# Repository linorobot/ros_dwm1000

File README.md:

first of all this is an awesome project guys you can edit it and make it more better.
this is a positioning system which will work indoor and outdoor both.
hope u all like it:)

# ros_dwm1000

ROS Indoor/Outdoor Positioning System based on Decawave's DWM1000 Ultra Wide Band transceivers.
The whole system was tested indoors with 3 anchors and 1 tag. Technically this should work outdoors as well.

### Hardware
Both anchors and tags use the same circuit board. The board houses the UWB transceiver, an Arduino Pro Mini 3.3V and a built-in USB
Male so you can plug it straight to a power bank and deploy the anchors remotely.

1. If you wish to fabricate the PCB, the Gerber files are included /hardware/pcb/fabricate.
Seeedstudio's DRU for 2-layer board was used to verify the design.

2. The DWM1000 Arduino library  uses random address for the anchors and doesn't support arbitrary addresses.
You need to edit https://github.com/grassjelly/ros_dwm1000/blob/master/hardware/firmware/anchor/lib/DW1000/DW1000Ranging.cpp#L166-L167 every time you upload the
anchor codes to have unique address per anchor from:

    ```c++
    _currentShortAddress[0] = random(0, 256);
    _currentShortAddress[1] = random(0, 256);
    ```
    to the address you want (ie. address: '01'):

    ```c++
    _currentShortAddress[0] = 1;
    _currentShortAddress[1] = 0;
    ```

### Installation
1. Install dependencies

    ```sh
    $ pip install localization
    $ pip install scipy
    $ pip install shapely
    ```

2. Install map_server

    ```sh
    $ sudo apt-get install ros-indigo-map-server
    ```

3. Build the package

    ```sh
    $ cd ~/catkin_ws
    $ catkin_make
    ```

### Defining TF
1. You need to define the transforms from map to each anchor's frame. You can run map_server and load your map to identify
the exact points you want your anchors placed. Open RVIZ and click on the location of each anchor by using "Publish Points".

2. Once you get the exact location of each anchor, add the transforms in /launch/tf.launch file. Take note that the frame_id of
each anchor must be the same as the address defined in Arduino (_currentShortAddress[]).

### Usage
1. Run localize.launch:			

    ```sh
    $ roslaunch ros_dwm1000 localize.launch
    ```

### Parameters
##### serial_port(default: '/dev/ttyUSB0')
Tag's serial port.

##### frame_id(default: 'uwb_tag')
Tag's frame_id when transform's published from map to tag.

##### req_anchor(default: 3)
The mininum number of anchors the system must find before performing trilateration between anchors. Increase this if you want to improve the accuracy. This can be tweaked down to a minimum of 2 anchors. Each tag can only support up to 4 anchors now.

##### min_range(default: 0.5)
The minimum probable distance from an anchor to a tag to prevent false reading. For example, if your anchor is hanging 1 m away from
the floor, it makes sense to put 1 meter as minimum range since there's no way it will range less than 1 meter.

##### max_range(default: 10.0)
The maximum probable distance from an anchor to a tag to prevent false reading. For example, if your anchors are placed in 8 meter x 8 meter room,
you can set the max_range less than or equal the hypotenuse of the room since ranges won't get any longer than that.

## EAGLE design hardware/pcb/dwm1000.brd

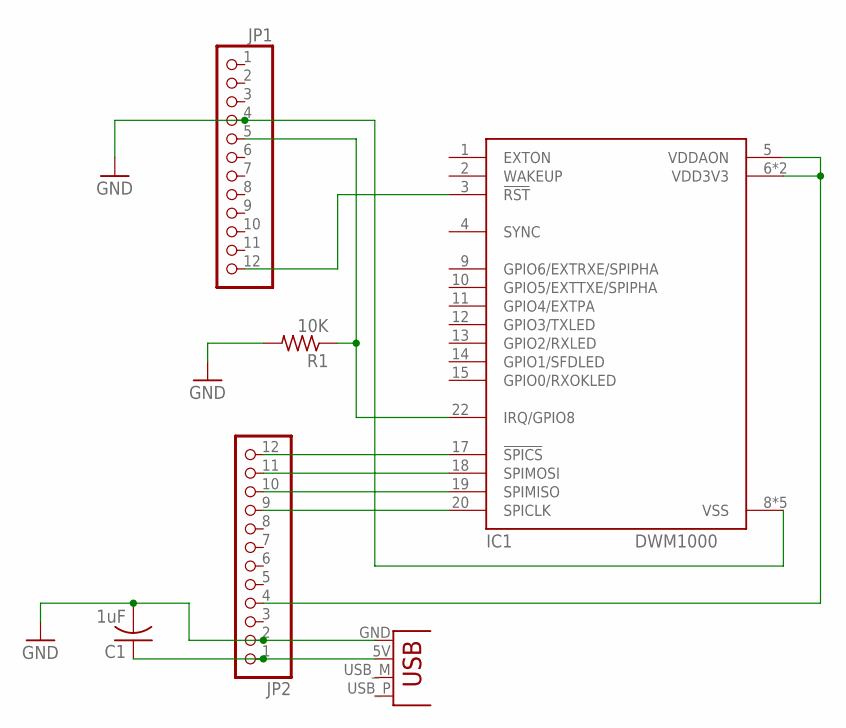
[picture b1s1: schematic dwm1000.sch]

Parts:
C1: 1uF; C025-024X044
IC1: DWM1000
JP1, JP2: PINHD-1X12; 1X12
JP3: USBPCB; USB-A-PCB
R1: 10K; 0207/7

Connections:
GND: C1.2, IC1.8 (VSS), IC1.16 (VSS), IC1.21 (VSS), IC1.23 (VSS), IC1.24 (VSS), JP1.4, JP2.2, JP3.GND, R1.2
unnamed: IC1.3 (!RST), JP1.12
unnamed: IC1.17 (!SPICS), JP2.12
unnamed: IC1.18 (SPIMOSI), JP2.11
unnamed: IC1.20 (SPICLK), JP2.9
unnamed: IC1.19 (SPIMISO), JP2.10
unnamed: IC1.22 (IRQ/GPIO8), JP1.5, R1.1
unnamed: C1.1, JP2.1, JP3.5V (VBUS)
unnamed: IC1.5 (VDDAON), IC1.6 (VDD3V3), IC1.7 (VDD3V3), JP2.4

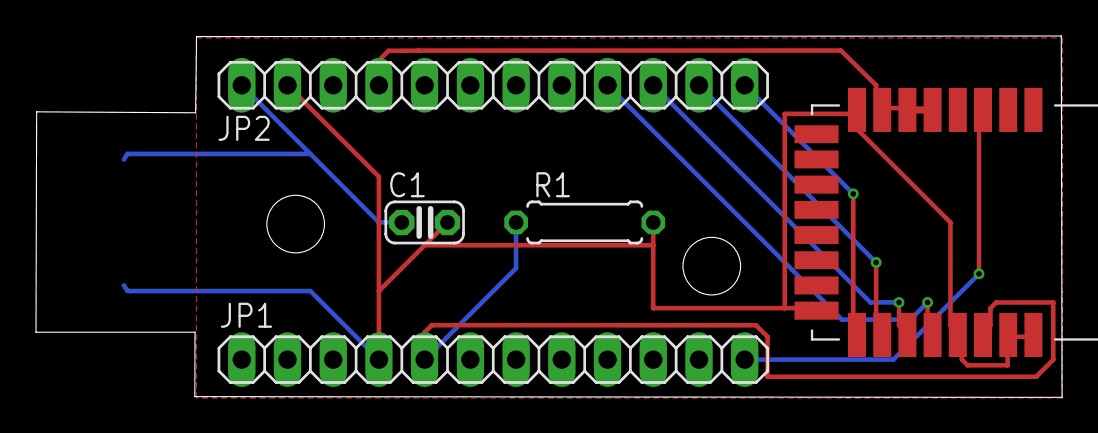
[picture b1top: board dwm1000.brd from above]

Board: 2 copper layers, 57.0 x 20.1 mm, 6 parts (1 on the bottom side), 9 nets.

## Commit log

2017-02-01 updated README file
2017-02-02 fixed bug
2017-02-02 added .gitignore
2017-03-03 changed library reference
2017-03-03 changed min_anchor to req_anchor param
2017-03-03 change launch file
2017-03-03 fixed formatting
2017-03-03 added comments
2017-03-03 added TODO for EKF integration
2017-03-03 changed beacon_count to anchors_found for readability
2017-05-02 fixed editing
2017-10-16 De-Dup Anchors

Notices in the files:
parts and their libraries:
SparkFun-Connectors: Licensing: CC v3.0 Share-Alike You are welcome to use this library for commercial purposes.
